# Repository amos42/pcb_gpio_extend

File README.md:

# SBC GPIO 확장 보드

---

[Raspberry Pi용 IO 확장](rasp_gpio_extend/)
([README.md](rasp_gpio_extend/README.md))

---

[Odroid N2(+)용 IO 확장](odroid_gpio_extend/)
([README.md](odroid_gpio_extend/README.md))

---

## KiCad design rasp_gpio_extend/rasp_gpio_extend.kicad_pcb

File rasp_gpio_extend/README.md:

# pi-extend 보드

라즈베리파이의 GPIO를 브레드보드로 연결하기 위한 커넥터 보드.

---
Raspberry pi 3 Pinout

회로도

PCB 이미지 앞면

PCB 이미지 뒷면

샘플 이미지

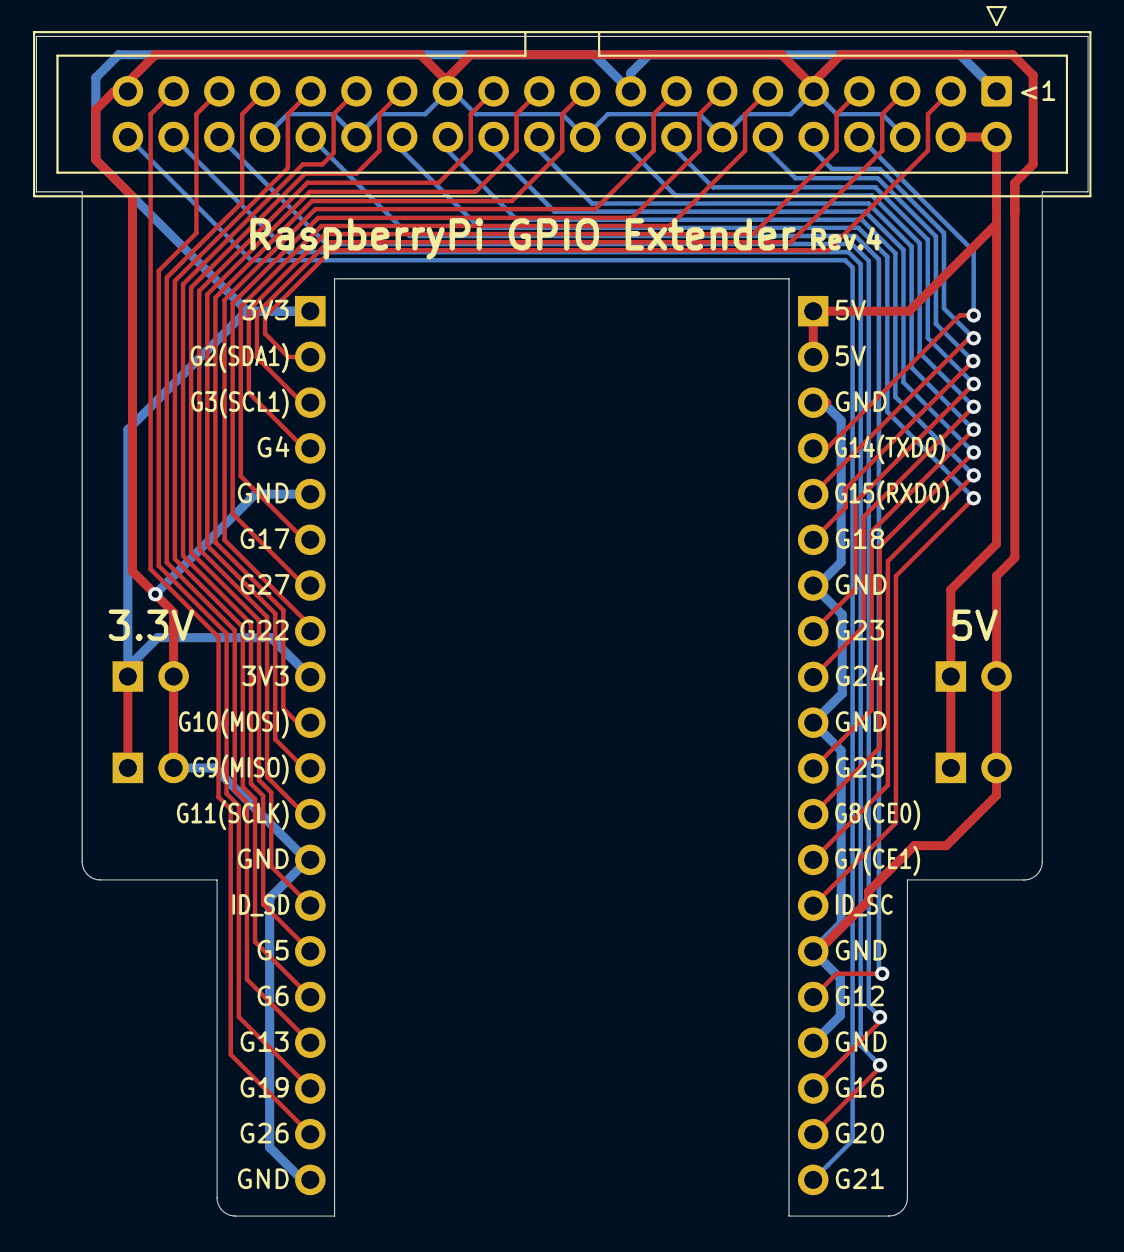
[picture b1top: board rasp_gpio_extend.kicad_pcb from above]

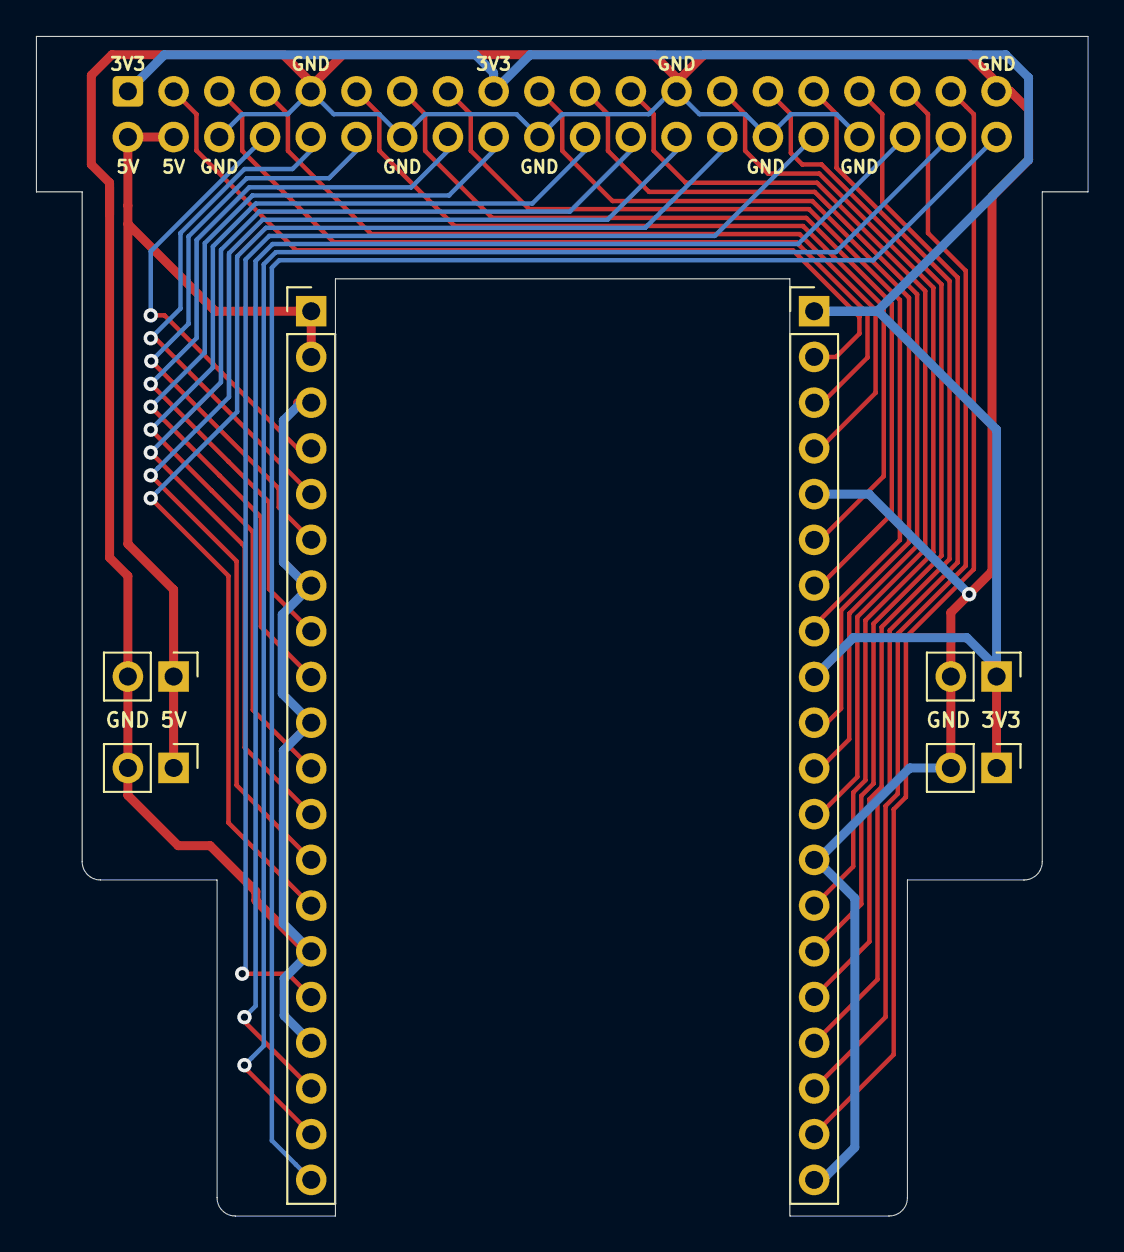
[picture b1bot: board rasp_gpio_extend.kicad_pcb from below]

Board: 2 copper layers, 58.4 x 65.5 mm, 7 parts (6 on the bottom side), 31 nets.

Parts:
J1: Conn_02x20_Odd_Even; IDC-Header_2x20_P2.54mm_Vertical
J2, J3: Conn_01x20_Male; PinHeader_1x20_P2.54mm_Vertical
J4, J5, J6, J7: Conn_01x02_Male; PinHeader_1x02_P2.54mm_Vertical

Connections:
+3V3: J1.1, J1.17, J2.1, J2.9, J4.1, J6.1
+5V: J1.2, J1.4, J3.1, J3.2, J5.1, J7.1
GND: J1.6, J1.9, J1.14, J1.20, J1.25, J1.30, J1.34, J1.39, J2.5, J2.13, J2.20, J3.3, J3.7, J3.10, J3.15, J3.17, J4.2, J5.2, J6.2, J7.2
unnamed: J1.3, J2.2
unnamed: J1.5, J2.3
unnamed: J1.7, J2.4
unnamed: J1.8, J3.4
unnamed: J1.10, J3.5
unnamed: J1.11, J2.6
unnamed: J1.12, J3.6
unnamed: J1.13, J2.7
unnamed: J1.15, J2.8
unnamed: J1.16, J3.8
unnamed: J1.18, J3.9
unnamed: J1.19, J2.10
unnamed: J1.21, J2.11
unnamed: J1.22, J3.11
unnamed: J1.23, J2.12
unnamed: J1.24, J3.12
unnamed: J1.26, J3.13
unnamed: J1.27, J2.14
unnamed: J1.28, J3.14
unnamed: J1.29, J2.15
unnamed: J1.31, J2.16
unnamed: J1.32, J3.16
unnamed: J1.33, J2.17
unnamed: J1.35, J2.18
unnamed: J1.36, J3.18
unnamed: J1.37, J2.19
unnamed: J1.38, J3.19
unnamed: J1.40, J3.20

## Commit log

2023-02-11 문서 링크 수정
